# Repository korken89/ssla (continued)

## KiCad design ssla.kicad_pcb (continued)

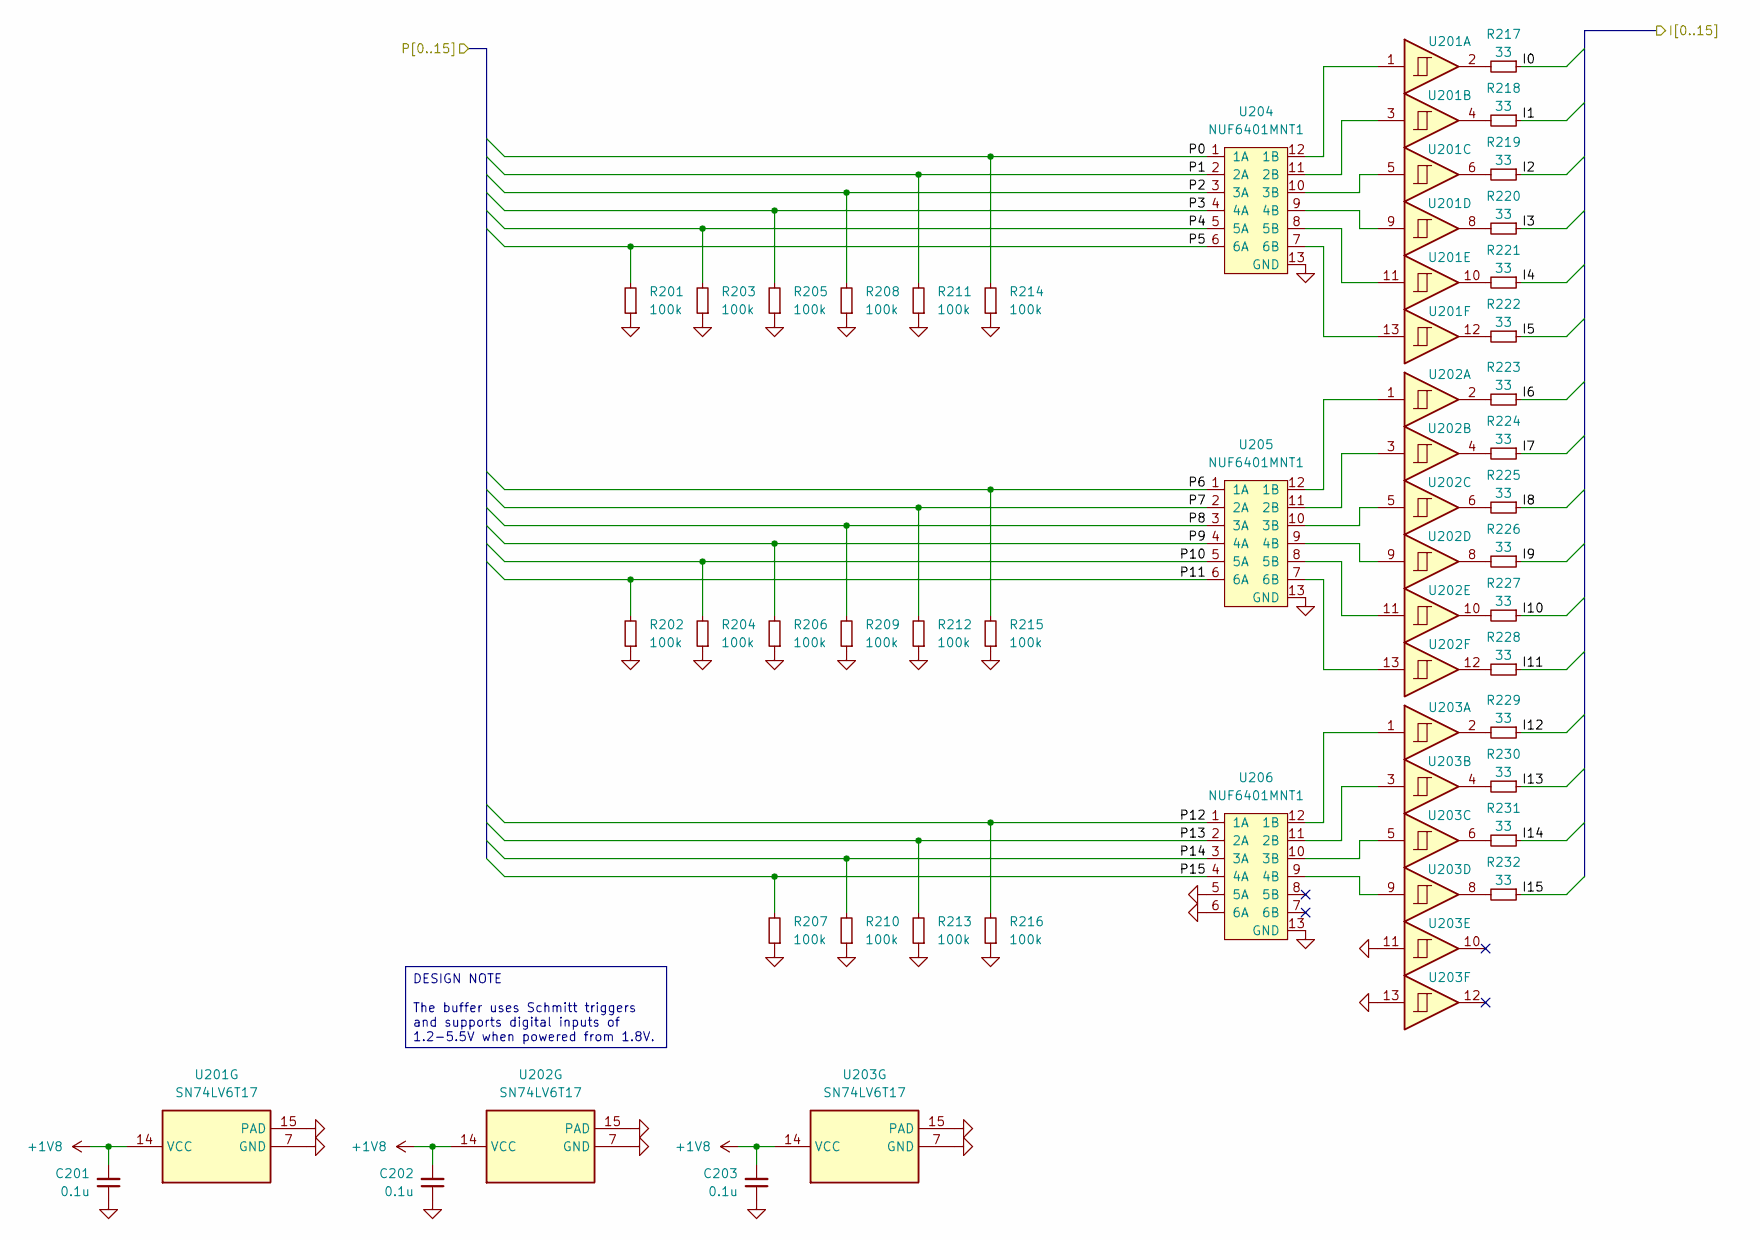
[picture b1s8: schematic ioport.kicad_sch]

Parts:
C201, C202, C203: 0.1u; C_0402_1005Metric; LCSC C307331
R201, R202, R203, R204, R205, R206, R207, R208, R209, R210, R211, R212, R213, R214, R215, R216: 100k; R_0402_1005Metric; LCSC C25741
R217, R218, R219, R220, R221, R222, R223, R224, R225, R226, R227, R228, R229, R230, R231, R232: 33; R_0402_1005Metric; LCSC C25105
U201, U202, U203: SN74LV6T17; DHVQFN-14-1EP_2.5x3mm_P0.5mm_EP1x1.5mm; LCSC C22428345
U204, U205, U206: NUF6401MNT1; DFN-12-1EP_1.35x3mm_P0.5mm; LCSC C233491

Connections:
+1V8: C201.2, C202.2, C203.2, U201.14 (VCC), U202.14 (VCC), U203.14 (VCC); also elsewhere on the board
/Logic Channels/P1.0: R214.2, U204.1 (1A); also elsewhere on the board
/Logic Channels/P1.1: R211.2, U204.2 (2A); also elsewhere on the board
/Logic Channels/P1.2: R208.2, U204.3 (3A); also elsewhere on the board
/Logic Channels/P1.3: R205.2, U204.4 (4A); also elsewhere on the board
/Logic Channels/P1.4: R203.2, U204.5 (5A); also elsewhere on the board
/Logic Channels/P1.5: R201.2, U204.6 (6A); also elsewhere on the board
/Logic Channels/P1.6: R215.2, U205.1 (1A); also elsewhere on the board
/Logic Channels/P1.7: R212.2, U205.2 (2A); also elsewhere on the board
/Logic Channels/P1.8: R209.2, U205.3 (3A); also elsewhere on the board
/Logic Channels/P1.9: R206.2, U205.4 (4A); also elsewhere on the board
/Logic Channels/P1.10: R204.2, U205.5 (5A); also elsewhere on the board
/Logic Channels/P1.11: R202.2, U205.6 (6A); also elsewhere on the board
/Logic Channels/P1.12: R216.2, U206.1 (1A); also elsewhere on the board
/Logic Channels/P1.13: R213.2, U206.2 (2A); also elsewhere on the board
/Logic Channels/P1.14: R210.2, U206.3 (3A); also elsewhere on the board
/Logic Channels/P1.15: R207.2, U206.4 (4A); also elsewhere on the board
/Logic Channels/PORT1_I0: R217.1; also elsewhere on the board
/Logic Channels/PORT1_I1: R218.1; also elsewhere on the board
/Logic Channels/PORT1_I2: R219.1; also elsewhere on the board
/Logic Channels/PORT1_I3: R220.1; also elsewhere on the board
/Logic Channels/PORT1_I4: R221.1; also elsewhere on the board
/Logic Channels/PORT1_I5: R222.1; also elsewhere on the board
/Logic Channels/PORT1_I6: R223.1; also elsewhere on the board
/Logic Channels/PORT1_I7: R224.1; also elsewhere on the board
/Logic Channels/PORT1_I8: R225.1; also elsewhere on the board
/Logic Channels/PORT1_I9: R226.1; also elsewhere on the board
/Logic Channels/PORT1_I10: R227.1; also elsewhere on the board
/Logic Channels/PORT1_I11: R228.1; also elsewhere on the board
/Logic Channels/PORT1_I12: R229.1; also elsewhere on the board
/Logic Channels/PORT1_I13: R230.1; also elsewhere on the board
/Logic Channels/PORT1_I14: R231.1; also elsewhere on the board
/Logic Channels/PORT1_I15: R232.1; also elsewhere on the board
GND: C201.1, C202.1, C203.1, R201.1, R202.1, R203.1, R204.1, R205.1, R206.1, R207.1, R208.1, R209.1, R210.1, R211.1, R212.1, R213.1, R214.1, R215.1, R216.1, U201.7 (GND), U201.15 (PAD), U202.7 (GND), U202.15 (PAD), U203.7 (GND), U203.11, U203.13, U203.15 (PAD), U204.13 (GND), U205.13 (GND), U206.5 (5A), U206.6 (6A), U206.13 (GND); also elsewhere on the board
unnamed: R217.2, U201.2
unnamed: R218.2, U201.4
unnamed: R219.2, U201.6
unnamed: R220.2, U201.8
unnamed: R221.2, U201.10
unnamed: R222.2, U201.12
unnamed: R223.2, U202.2
unnamed: R224.2, U202.4
unnamed: R225.2, U202.6
unnamed: R226.2, U202.8
unnamed: R227.2, U202.10
unnamed: R228.2, U202.12
unnamed: R229.2, U203.2
unnamed: R230.2, U203.4
unnamed: R231.2, U203.6
unnamed: R232.2, U203.8
unnamed: U201.1, U204.12 (1B)
unnamed: U201.3, U204.11 (2B)
unnamed: U201.5, U204.10 (3B)
unnamed: U201.9, U204.9 (4B)
unnamed: U201.11, U204.8 (5B)
unnamed: U201.13, U204.7 (6B)
unnamed: U202.1, U205.12 (1B)
unnamed: U202.3, U205.11 (2B)
unnamed: U202.5, U205.10 (3B)
unnamed: U202.9, U205.9 (4B)
unnamed: U202.11, U205.8 (5B)
unnamed: U202.13, U205.7 (6B)
unnamed: U203.1, U206.12 (1B)
unnamed: U203.3, U206.11 (2B)
unnamed: U203.5, U206.10 (3B)
unnamed: U203.9, U206.9 (4B)

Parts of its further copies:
C301, C302, C303: 0.1u; C_0402_1005Metric; LCSC C307331
R301, R302, R303, R304, R305, R306, R307, R308, R309, R310, R311, R312, R313, R314, R315, R316: 100k; R_0402_1005Metric; LCSC C25741
R317, R318, R319, R320, R321, R322, R323, R324, R325, R326, R327, R328, R329, R330, R331, R332: 33; R_0402_1005Metric; LCSC C25105
U301, U302, U303: SN74LV6T17; DHVQFN-14-1EP_2.5x3mm_P0.5mm_EP1x1.5mm; LCSC C22428345
U304, U305, U306: NUF6401MNT1; DFN-12-1EP_1.35x3mm_P0.5mm; LCSC C233491

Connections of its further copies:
+1V8: C301.2, C302.2, C303.2, U301.14 (VCC), U302.14 (VCC), U303.14 (VCC); also elsewhere on the board
/Logic Channels/P2.0: R314.2, U304.1 (1A); also elsewhere on the board
/Logic Channels/P2.1: R311.2, U304.2 (2A); also elsewhere on the board
/Logic Channels/P2.2: R308.2, U304.3 (3A); also elsewhere on the board
/Logic Channels/P2.3: R305.2, U304.4 (4A); also elsewhere on the board
/Logic Channels/P2.4: R303.2, U304.5 (5A); also elsewhere on the board
/Logic Channels/P2.5: R301.2, U304.6 (6A); also elsewhere on the board
/Logic Channels/P2.6: R315.2, U305.1 (1A); also elsewhere on the board
/Logic Channels/P2.7: R312.2, U305.2 (2A); also elsewhere on the board
/Logic Channels/P2.8: R309.2, U305.3 (3A); also elsewhere on the board
/Logic Channels/P2.9: R306.2, U305.4 (4A); also elsewhere on the board
/Logic Channels/P2.10: R304.2, U305.5 (5A); also elsewhere on the board
/Logic Channels/P2.11: R302.2, U305.6 (6A); also elsewhere on the board
/Logic Channels/P2.12: R316.2, U306.1 (1A); also elsewhere on the board
/Logic Channels/P2.13: R313.2, U306.2 (2A); also elsewhere on the board
/Logic Channels/P2.14: R310.2, U306.3 (3A); also elsewhere on the board
/Logic Channels/P2.15: R307.2, U306.4 (4A); also elsewhere on the board
/Logic Channels/PORT2_I0: R317.1; also elsewhere on the board
/Logic Channels/PORT2_I1: R318.1; also elsewhere on the board
/Logic Channels/PORT2_I2: R319.1; also elsewhere on the board
/Logic Channels/PORT2_I3: R320.1; also elsewhere on the board
/Logic Channels/PORT2_I4: R321.1; also elsewhere on the board
/Logic Channels/PORT2_I5: R322.1; also elsewhere on the board
/Logic Channels/PORT2_I6: R323.1; also elsewhere on the board
/Logic Channels/PORT2_I7: R324.1; also elsewhere on the board
/Logic Channels/PORT2_I8: R325.1; also elsewhere on the board
/Logic Channels/PORT2_I9: R326.1; also elsewhere on the board
/Logic Channels/PORT2_I10: R327.1; also elsewhere on the board
/Logic Channels/PORT2_I11: R328.1; also elsewhere on the board
/Logic Channels/PORT2_I12: R329.1; also elsewhere on the board
/Logic Channels/PORT2_I13: R330.1; also elsewhere on the board
/Logic Channels/PORT2_I14: R331.1; also elsewhere on the board
/Logic Channels/PORT2_I15: R332.1; also elsewhere on the board
GND: C301.1, C302.1, C303.1, R301.1, R302.1, R303.1, R304.1, R305.1, R306.1, R307.1, R308.1, R309.1, R310.1, R311.1, R312.1, R313.1, R314.1, R315.1, R316.1, U301.7 (GND), U301.15 (PAD), U302.7 (GND), U302.15 (PAD), U303.7 (GND), U303.11, U303.13, U303.15 (PAD), U304.13 (GND), U305.13 (GND), U306.5 (5A), U306.6 (6A), U306.13 (GND); also elsewhere on the board
unnamed: R317.2, U301.2
unnamed: R318.2, U301.4
unnamed: R319.2, U301.6
unnamed: R320.2, U301.8
unnamed: R321.2, U301.10
unnamed: R322.2, U301.12
unnamed: R323.2, U302.2
unnamed: R324.2, U302.4
unnamed: R325.2, U302.6
unnamed: R326.2, U302.8
unnamed: R327.2, U302.10
unnamed: R328.2, U302.12
unnamed: R329.2, U303.2
unnamed: R330.2, U303.4
unnamed: R331.2, U303.6
unnamed: R332.2, U303.8
unnamed: U301.1, U304.12 (1B)
unnamed: U301.3, U304.11 (2B)
unnamed: U301.5, U304.10 (3B)
unnamed: U301.9, U304.9 (4B)
unnamed: U301.11, U304.8 (5B)
unnamed: U301.13, U304.7 (6B)
unnamed: U302.1, U305.12 (1B)
unnamed: U302.3, U305.11 (2B)
unnamed: U302.5, U305.10 (3B)
unnamed: U302.9, U305.9 (4B)
unnamed: U302.11, U305.8 (5B)
unnamed: U302.13, U305.7 (6B)
unnamed: U303.1, U306.12 (1B)
unnamed: U303.3, U306.11 (2B)
unnamed: U303.5, U306.10 (3B)
unnamed: U303.9, U306.9 (4B)

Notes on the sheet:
DESIGN NOTE The buffer uses Schmitt triggers and supports digital inputs of 1.2-5.5V when powered from 1.8V.

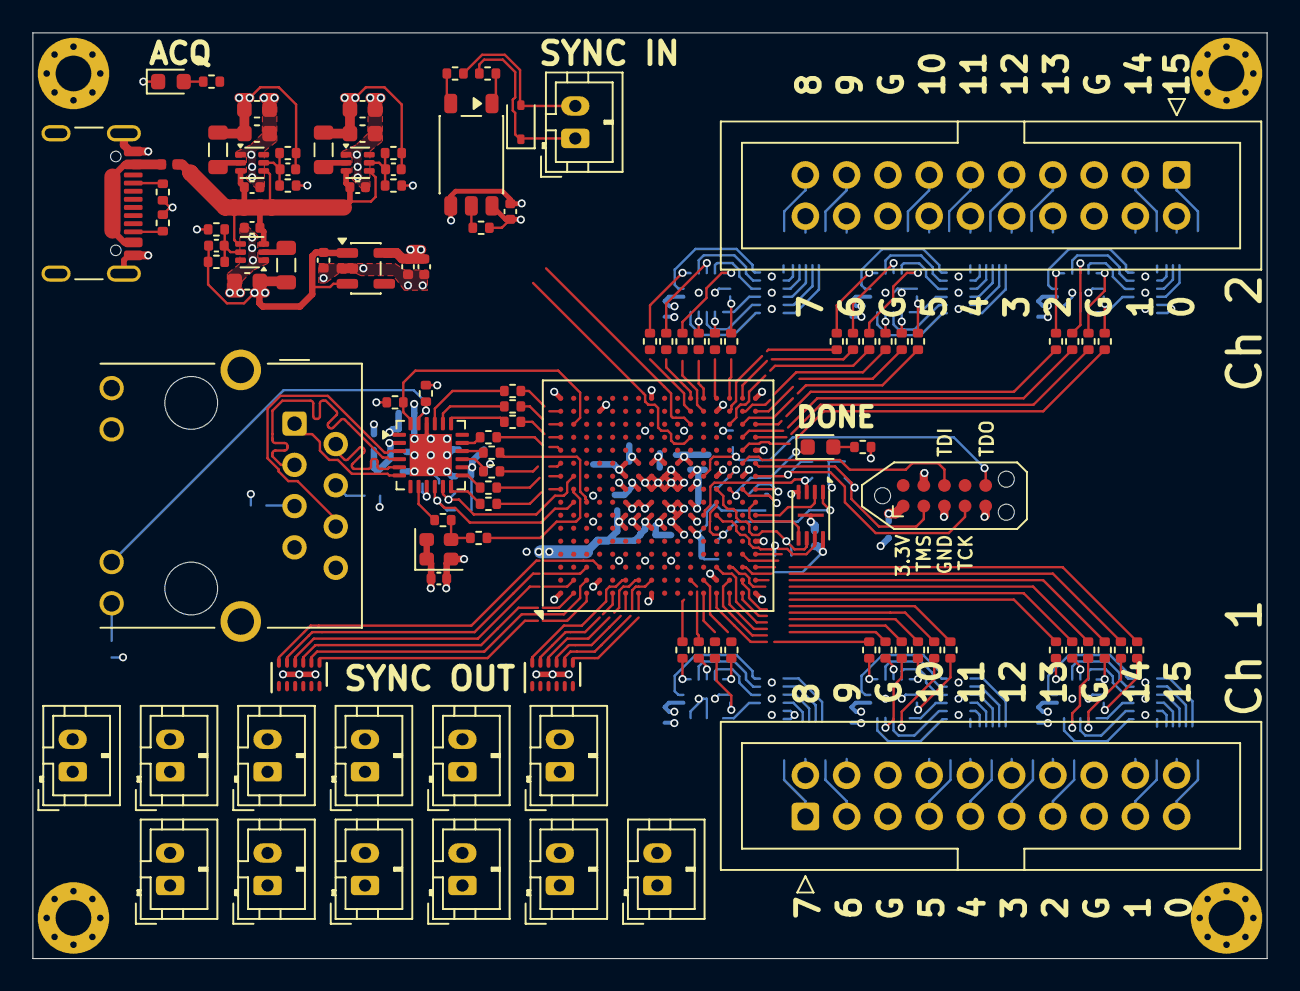
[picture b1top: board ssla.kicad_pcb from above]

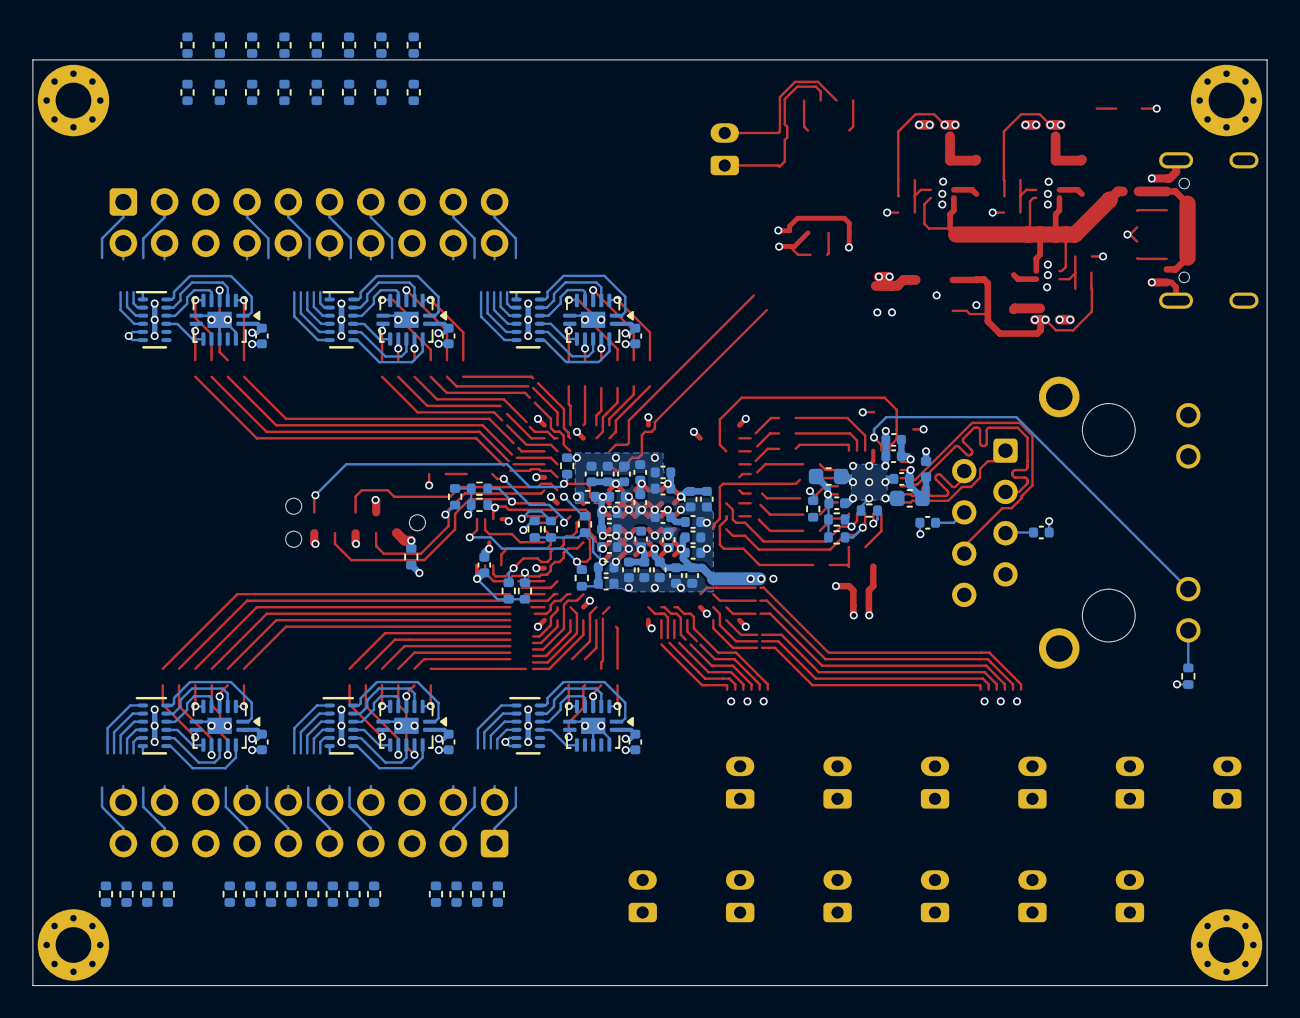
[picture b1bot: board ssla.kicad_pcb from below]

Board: 4 copper layers, 76.0 x 57.0 mm, 216 parts (103 on the bottom side), 223 nets.

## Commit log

2024-11-09 Save
2024-11-10 0 unrouted
2024-11-11 LCSC part numbers, started moving to through-hole IDC connector
2024-11-12 Started move to ECP5
2024-11-13 Ordered
2024-11-19 Add script for printing all IO lines sorted by number
